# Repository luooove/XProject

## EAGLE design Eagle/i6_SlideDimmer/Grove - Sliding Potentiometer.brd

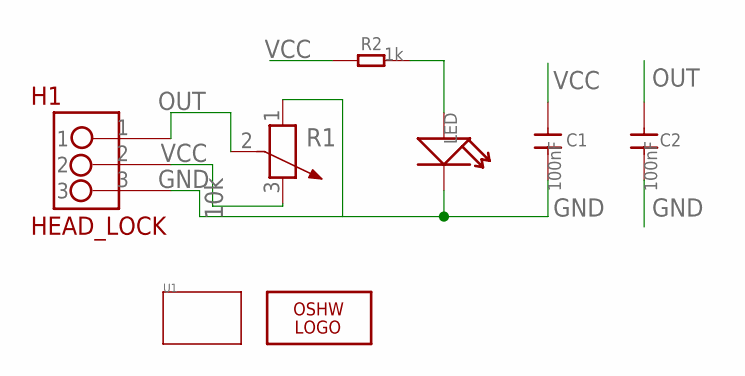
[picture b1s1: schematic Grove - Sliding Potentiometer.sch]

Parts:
C1, C2: 100nF; 0805
H1: HEAD_LOCK
LED: LED'0805'; LED-0805
LOGO1: LOGO-OSHW-FILLX0200-NT; OSHW_FILLX200_NOTEXT
R1: 10k; 3P-SQUA-45.6X10X5.8H
R2: 1k; 0805
U1: TWIG'3U'; 3U-DIM-W/-DRILL

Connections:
GND: C1.2, C2.2, H1.3, LED.-, R1.1
unnamed: LED.+, R2.2
OUT: C2.1, H1.1, R1.2 (3)
VCC: C1.1, H1.2, R1.3 (2)

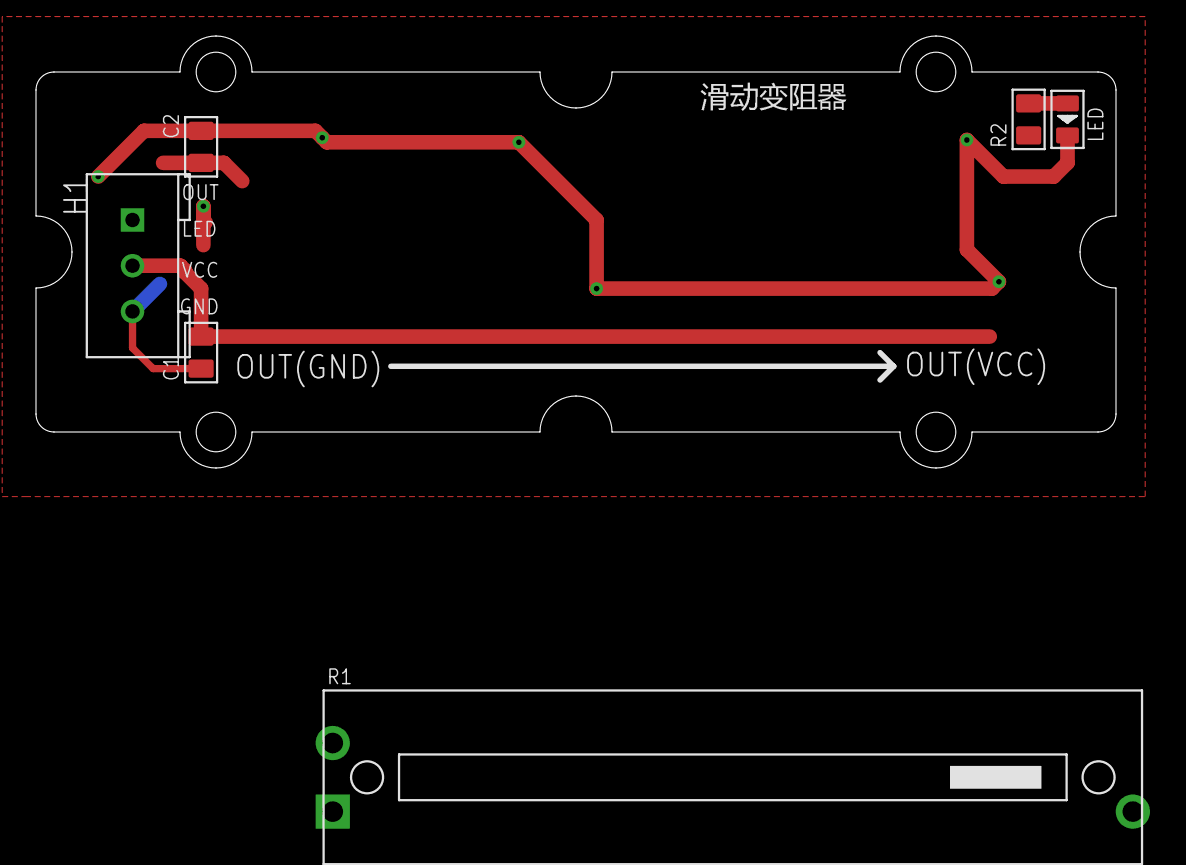
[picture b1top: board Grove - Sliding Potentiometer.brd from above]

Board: 2 copper layers, 60.0 x 24.0 mm, 8 parts (1 on the bottom side), 4 nets.

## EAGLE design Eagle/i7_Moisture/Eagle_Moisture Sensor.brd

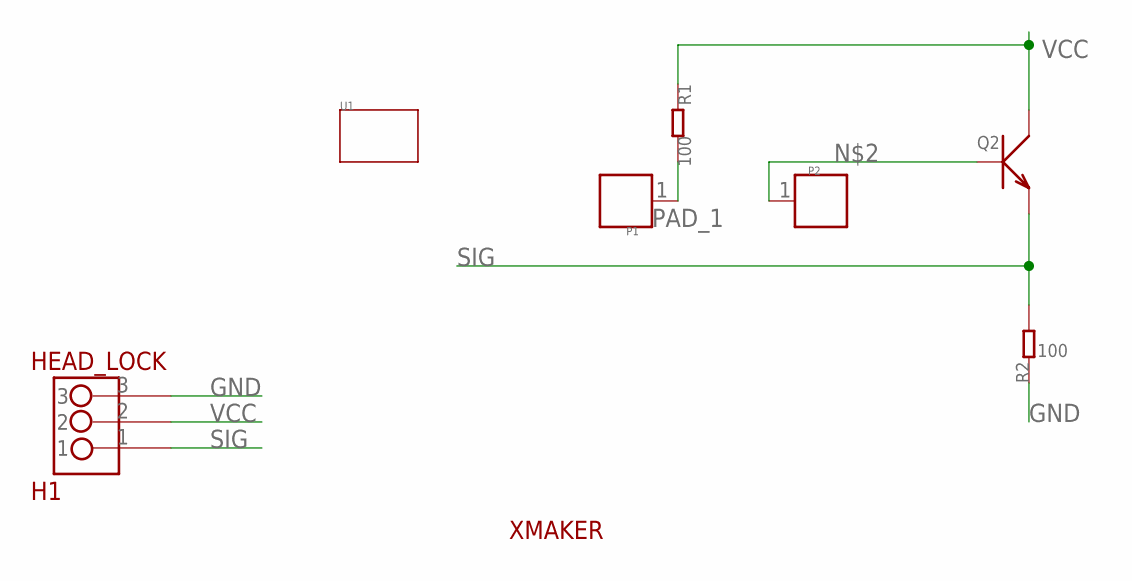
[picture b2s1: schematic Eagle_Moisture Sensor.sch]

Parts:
H1: HEAD_LOCK
P1, P2: PAD.03; 1P-SMD-0.76X0.76
Q2: TRANSISTOR-NPN-SOT23''; SOT23
R1, R2: 100; 0603
U1: TWIG'SPECIAL'; 3U-DIM-W/-DRILL-SPECIAL
U$1: XMAKERLOGO2

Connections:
GND: H1.3, R2.1
unnamed: P2.1, Q2.1 (B)
PAD_1: P1.1, R1.2
SIG: H1.1, Q2.2 (E), R2.2
VCC: H1.2, Q2.3 (C), R1.1

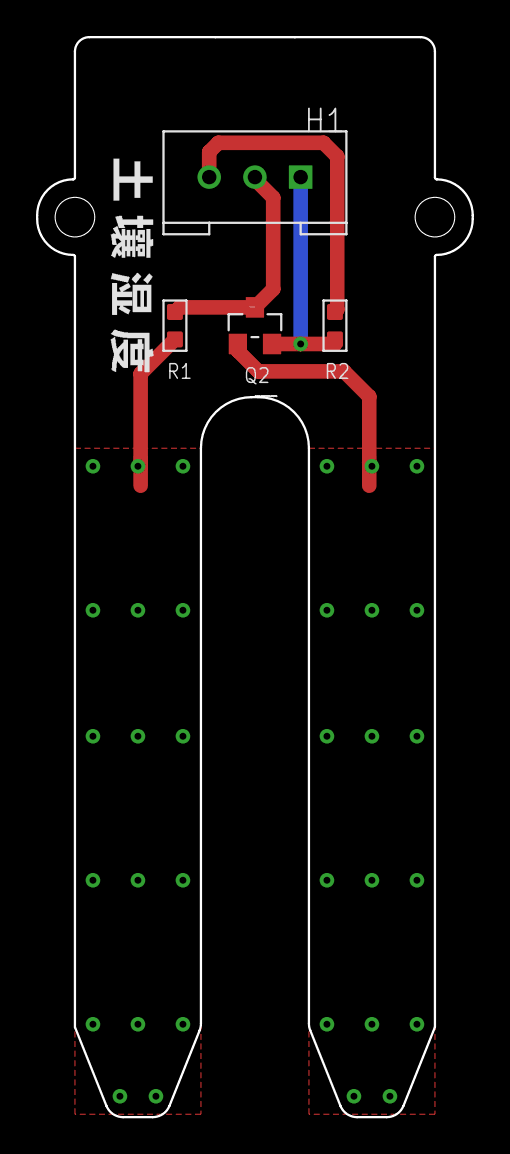
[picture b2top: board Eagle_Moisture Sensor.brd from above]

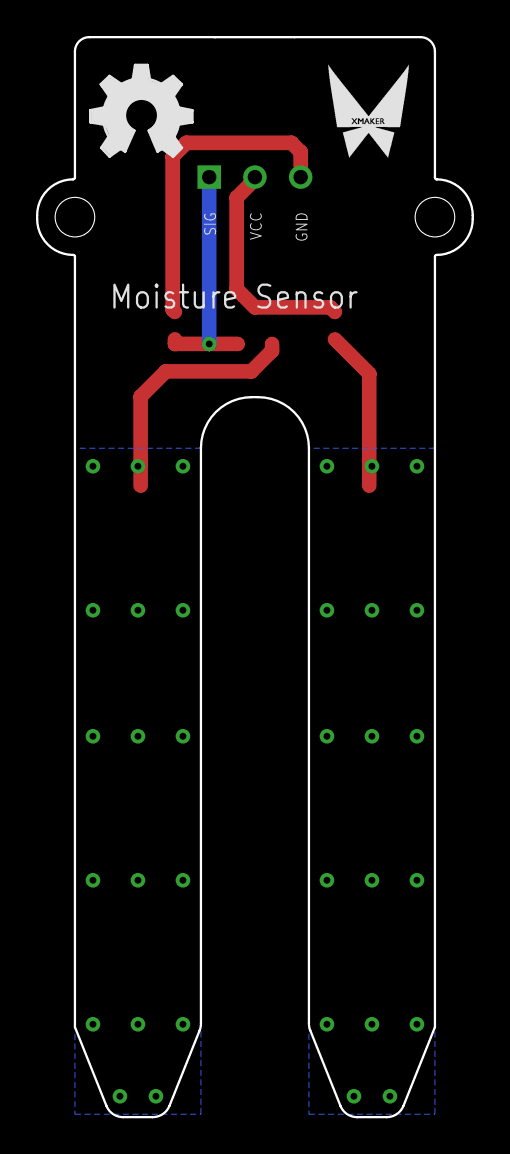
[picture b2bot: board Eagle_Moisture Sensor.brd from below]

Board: 2 copper layers, 24.2 x 60.0 mm, 9 parts (2 on the bottom side), 5 nets.

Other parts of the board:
U$2: OSHW_FILLX200_NOTEXT

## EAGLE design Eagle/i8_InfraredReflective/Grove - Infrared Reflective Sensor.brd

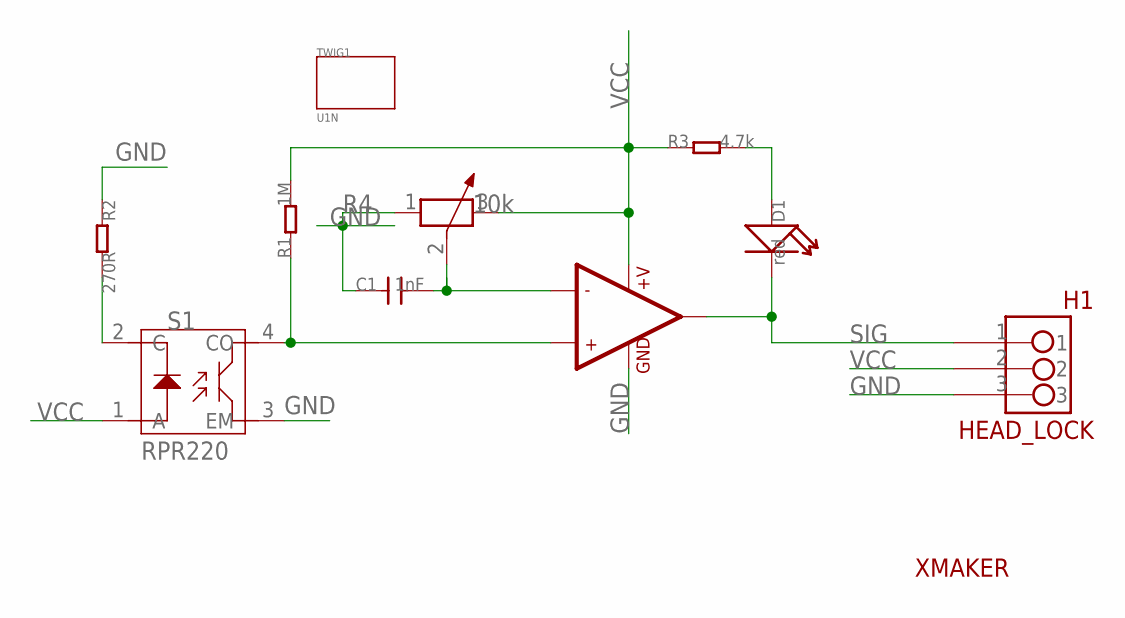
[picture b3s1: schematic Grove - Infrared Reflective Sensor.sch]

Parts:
C1: 1nF; 0603
D1: red; LED0603
H1: HEAD_LOCK
R1: 1M; 0603_S
R2: 270R; 0603_S
R3: 4.7k; 0603_S
R4: 10k; 3P-SQUA-6.7X6.4
S1: RPR220; 4P-6.4X4.9X6.5H
TWIG1: U1N
U1: 002-LMV358; SO08
U$3: XMAKERLOGO2

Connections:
GND: C1.1, H1.3, R2.1, R4.1, S1.3 (EM), U1.4 (GND)
unnamed: C1.2, R4.2 (3), U1.2 (-IN1)
unnamed: R1.1, S1.4 (CO), U1.3 (+IN1)
unnamed: R2.2, S1.2 (C)
unnamed: D1.1 (+), R3.2
SIG: D1.2 (-), H1.1, U1.1 (OUT1)
VCC: H1.2, R1.2, R3.1, R4.3 (2), S1.1 (A), U1.8 (+V)

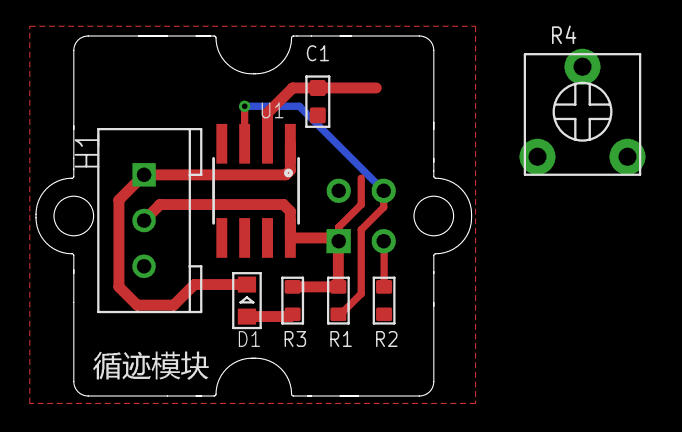
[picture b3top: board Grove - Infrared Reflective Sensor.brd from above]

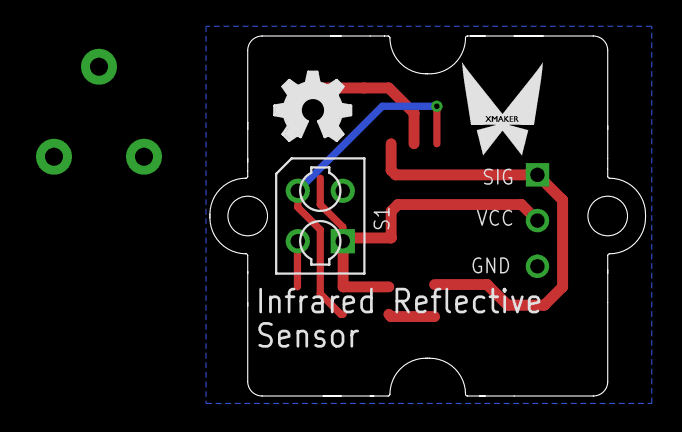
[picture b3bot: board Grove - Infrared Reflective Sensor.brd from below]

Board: 2 copper layers, 24.2 x 20.0 mm, 12 parts (3 on the bottom side), 7 nets.

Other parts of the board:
U$1: OSHW_FILLX150_NOTEXT

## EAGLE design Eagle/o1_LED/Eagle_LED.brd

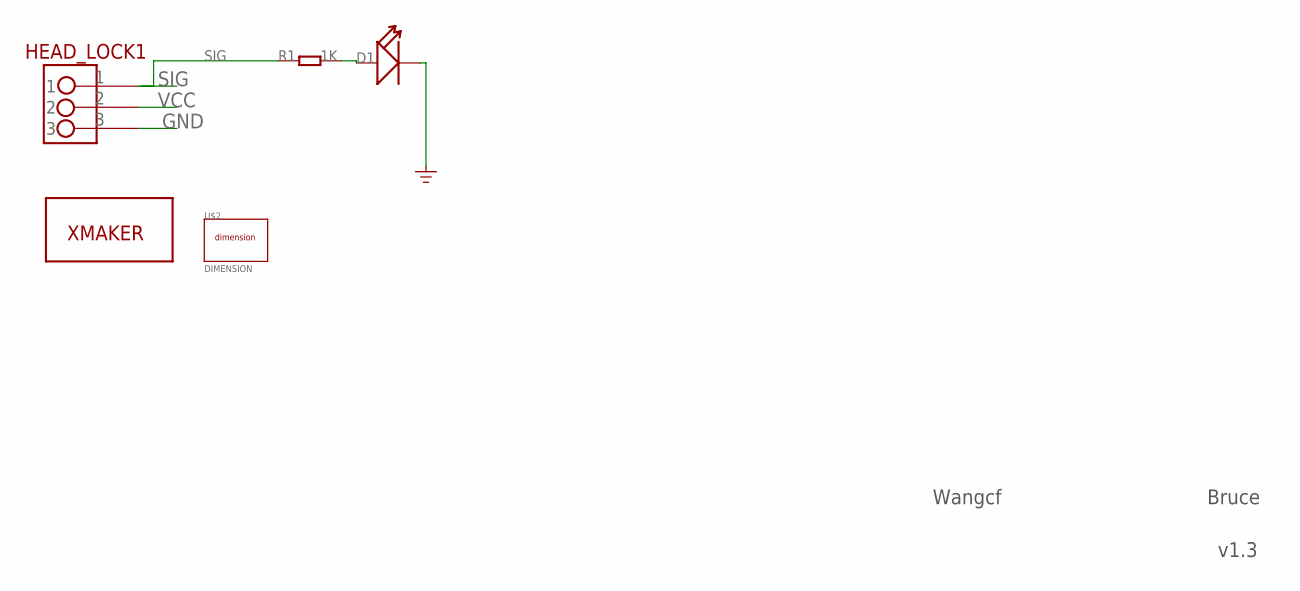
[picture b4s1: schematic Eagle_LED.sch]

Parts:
D1: LED-6MM; LED-2P-2.54-6MM
HEAD_LOCK1: HEAD_LOCK
R1: 1K; 0603
U$2: DIMENSION
U$4: XMAKERLOGO

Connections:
GND: D1.-, HEAD_LOCK1.3
unnamed: D1.+, R1.2
SIG: HEAD_LOCK1.1, R1.1
VCC: HEAD_LOCK1.2

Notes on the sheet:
Wangcf
v1.3
Bruce

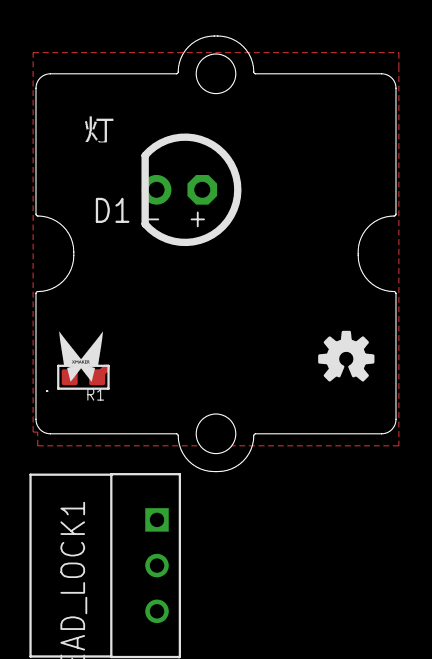
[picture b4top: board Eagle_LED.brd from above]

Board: 2 copper layers, 20.0 x 24.2 mm, 6 parts (0 on the bottom side), 3 nets.

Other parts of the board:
U$6: OSHW-LOGO-S

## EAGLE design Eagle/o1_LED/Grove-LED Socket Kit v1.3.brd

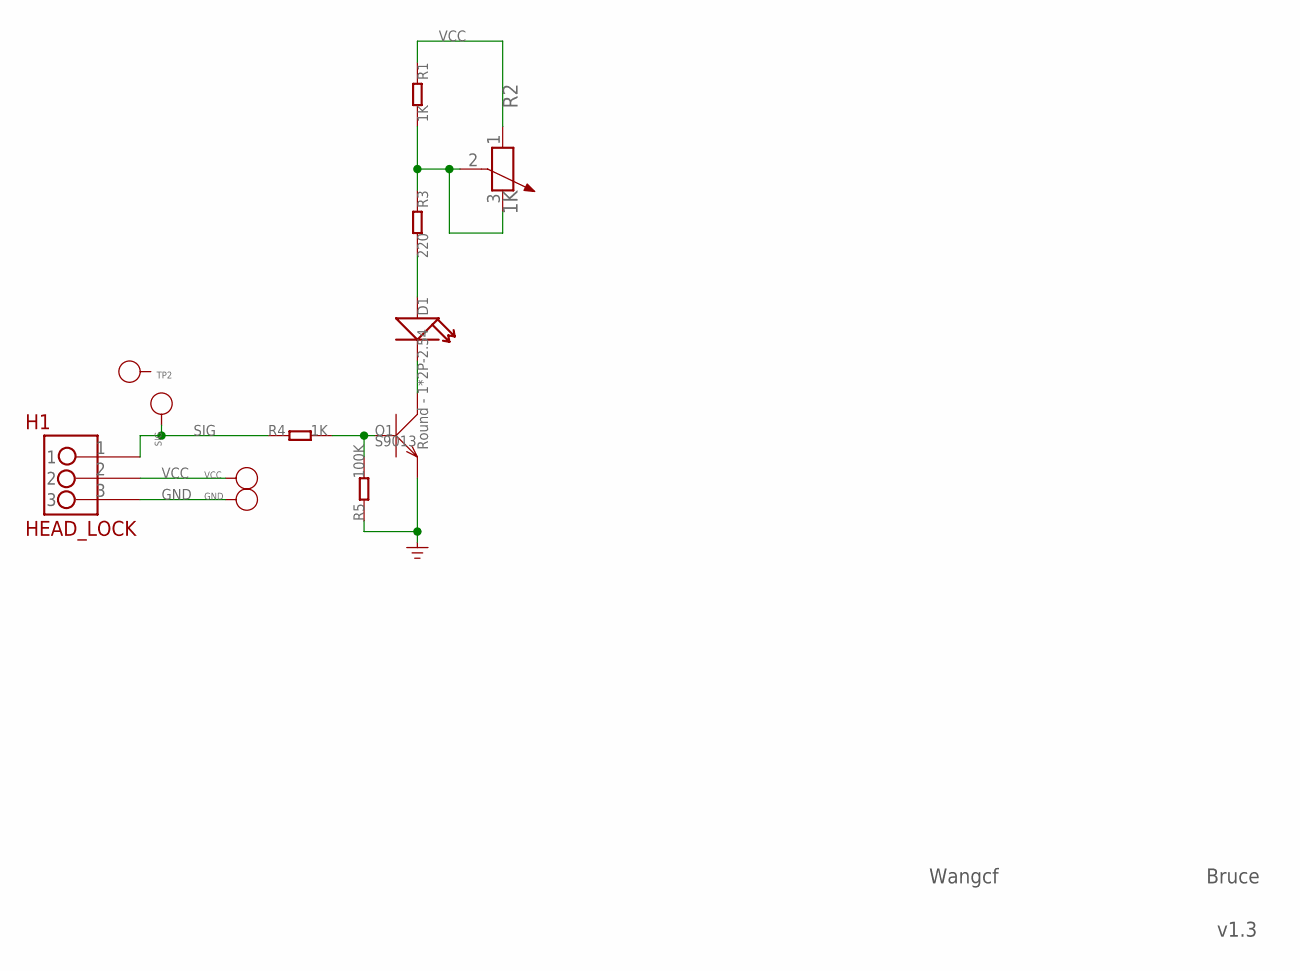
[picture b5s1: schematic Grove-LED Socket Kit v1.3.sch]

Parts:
D1: Round - 1*2P-2.54; LED-2P-2.54-6MM
GND: PAD-TEST-POINT'4545'; TP_4545
H1: HEAD_LOCK
Q1: S9013; SOT23
R1, R4: 1K; 0603
R2: 1K; 3P-SQUA-6.7X6.4
R3: 220; 0603
R5: 100K; 0603
SIG: PAD-TEST-POINT'4545'; TP_4545
TP2: PAD-TEST-POINT'4545'; TP_4545
VCC: PAD-TEST-POINT'4545'; TP_4545

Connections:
GND: GND.T, H1.3, Q1.2 (E), R5.1
unnamed: R1.2, R2.2 (3), R2.3 (2), R3.1
unnamed: D1.-, Q1.3 (C)
unnamed: D1.+, R3.2
unnamed: Q1.1 (B), R4.2, R5.2
SIG: H1.1, R4.1, SIG.T
VCC: H1.2, R1.1, R2.1, VCC.T

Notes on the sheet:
Wangcf
v1.3
Bruce

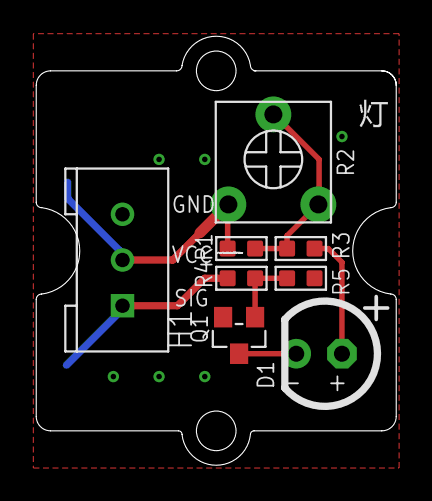
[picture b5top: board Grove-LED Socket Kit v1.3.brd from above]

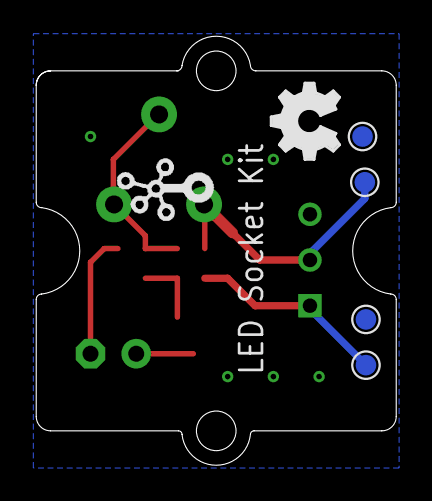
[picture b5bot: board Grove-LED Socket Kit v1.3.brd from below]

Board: 2 copper layers, 20.0 x 23.8 mm, 15 parts (6 on the bottom side), 7 nets.

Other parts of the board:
U$2: 1U-DIM-W/-DRILL
U$5: TWIGLOGO_SMALL
U$6: OSHW_FILLX150_NOTEXT

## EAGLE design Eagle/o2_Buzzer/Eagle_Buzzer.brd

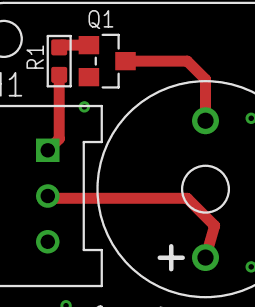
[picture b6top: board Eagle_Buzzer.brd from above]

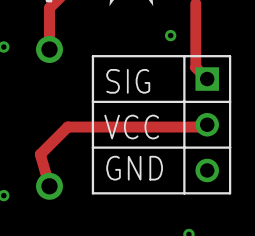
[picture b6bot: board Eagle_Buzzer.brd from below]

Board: 2 copper layers, 8 parts (2 on the bottom side), 5 nets.

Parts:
BUZ1: 2P-7.6-D12X6.5H
H1: HEAD_LOCK_3PIN_2
Q1: S9013; SOT23
R1: 1K; R0603
U$4: DIMENSION_2MM2MM; DIMENSION_2MM*2MM
U$5: XMAKERLOGO_2.5MM_TOP
U$6: OPENHARDWARE_2.5MM_TOP; OPENSOURCELOGO_2.5MM
U$7: NAME_BUZZER

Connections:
D1: H1.1, R1.1
DRI: BUZ1.-, Q1.3
GND: H1.3, Q1.2
unnamed: Q1.1, R1.2
VCC: BUZ1.+, H1.2

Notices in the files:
parts and their libraries:
SparkFun-Aesthetics: Licensing: Creative Commons ShareAlike 4.0 International - https://creativecommons.org/licenses/by-sa/4.0
